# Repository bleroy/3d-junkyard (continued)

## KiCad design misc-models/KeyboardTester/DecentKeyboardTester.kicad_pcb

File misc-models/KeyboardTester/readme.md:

# Decent Retro Keyboard Tester

The Decent Retro Keyboard Tester is an open source board designed around the RP2040 chip
to test vintage computer keyboards.
I built it to test my own modern keyboard replacements for Atari 8-bit computers, but
the architecture is generic enough that drivers for other computers should be very easy
to build.

The tester currently supports the following keyboards:

- Atari 400
- Atari 800
- Atari XE (except XEGS, coming soon)
- Atari 600XL and 800XL
- Atari 1200XL
- USB keyboards

## How to use the tester

Connect the tester to a power source (either the micro-USB at the back or the barrel jack,
center-positive with 5V).

Press the mode button repeatedly until you reach the mode for the keyboard to test.

Connect the keyboard to test.

Start pressing each key on the keyboard. The corresponding LED on the tester should turn
from orange to green. Continue doing that until all the lights are green.

If a light remains orange after the corresponding key has been pressed, there is an issue
with that key. Oftentimes, a whole pattern of keys will fail, not just one.
That usually means that a whole line or column of the keyboard matrix is failing.
Consult a map of the keyboard's matrix and probe the corresponding lines on the PCB or on the
keyboard cable.

## How to build one

### The board

The assembled board can be ordered from JLCPCB or PCBWay using the following files:

- [Gerber](./production/Decent_Retro_Keyboard_Tester_2.zip)
- [BOM](./production/bom.csv)
- [Positions](./production/positions.csv)

You should order the boards assembled, and you'll only have to solder the connectors,
the OLED screen and the barrel jack if you want to power the board without USB.

The connectors are:

- 24P 2.54mm male pin headers on the left of the board
- 15P 2.54mm male pin headers immediately to the right of the 24P connector
- 22P 2.54mm female headers on the top of the board
- 18P 2.54mm male pin headers under the 22P one.
- DB15 at the bottom left of the board
- USB-A connector to the right of the DB25 connector

Don't solder the display yet, as it's easier to do once the board is in the top half of the enclosure.

### The enclosure

Print the following parts:

- 1x [Enclosure top](./Enclosure/Decent%20Retro%20Keyboard%20Tester%20Enclosure-Top.stl)
- 1x [Enclosure bottom](./Enclosure/Decent%20Retro%20Keyboard%20Tester%20Enclosure-Bottom.stl)
- 3x [Button](./Enclosure/Decent%20Retro%20Keyboard%20Tester%20Enclosure-Button.stl)
- 1x [Full light tunnel](./Enclosure/Decent%20Retro%20Keyboard%20Tester%20Enclosure-Light%20tunnels.stl)
- 1x [Switch slider](./Enclosure/Decent%20Retro%20Keyboard%20Tester%20Enclosure-Slider.stl)

Depending on the keyboards you want to test:

- 1x [Atari XE light tunnel](./Enclosure/Decent%20Retro%20Keyboard%20Tester%20Enclosure-ATARI-XE-Light%20tunnels.stl)
- 1x [Atari XL light tunnel](./Enclosure/Decent%20Retro%20Keyboard%20Tester%20Enclosure-ATARI-XL-Light%20tunnels.stl)

Add 4 threaded inserts to the top of the enclosure.

With the top of the enclosure upside-down on your workbench, add the three buttons, put the OLED
screen in position, then add the main board on top of that.

Make sure everything is properly aligned and level, then solder the screen to the board.

Add the slider to the little switch at the back of the board.

Put the bottom of the enclosure in place, then secure everything with 4 screws corresponding to the
threaded inserts you chose.

### Adapter boards

The tester has some connectors built-in, but the ultimate goal is to support a wide variety of
keyboards with exotic connectors.
For instance, Atari XE and XL computers use a single-sided 2.54mm 24 pin connector that is very
hard to source outside of scavenging it from a vintage motherboard.

To address this, the board presents 24 GPIOs on a standard pin header connector so one can build
adapter boards that translate that into specific connectors.

Have the adapter boards you need fabricated and assemble the required connectors on them.

At this moment, the only adapter board is for Atari XE and XL computers:

- [Gerber](./adapter-ATARI-XE-XL/production/adapter-ATARI-XE-XL.zip)

  It can be assembled by adding a 24P 2.54mm female header on the bottom of the board and to the right
  and an Atari keyboard connector on top to the left with the contacts on the left.

### Overlays

Each keyboard driver will do its own mapping of the physical keys to the array of LEDs on the tester.
To make things a little nicer to look at, there are overlays that are made with a printed light tunnel
and a small PCB with windows in the mask layer that let the light get diffused over each key
footprint.

There are overlays available for the following keyboards:

- Atari XE - [Gerber](./Overlays/XE-overlay/production/XE-overlay.zip) & [light tunnel](./Overlays/XE-overlay/Decent%20Retro%20Keyboard%20Tester%20Enclosure-ATARI-XE-Light%20tunnels.stl)
- Atari XL - [Gerber](./Overlays/XL-overlay/production/XL-overlay.zip) & [light tunnel](./Overlays/XL-overlay/Decent%20Retro%20Keyboard%20Tester%20Enclosure-ATARI-XL-Light%20tunnels.stl)

### Flashing the firmware

The tester can be programmed through its micro-usb port on the back.
Connect that port to a computer and it will appear as a disk drive.

There's a one-time operation which is to install CircuitPython on the device.
Get [the latest version for the Pi Pico](https://circuitpython.org/board/raspberry_pi_pico/) and
copy the uf2 file to the root of the device's file system.
The device will reboot and show a new file system.

If at a later date you need to upgrade your CircuitPython, you can do so by keeping the Boot
button pressed while you connect the device to your computer. You'll then be able to copy a new
uf2 file.

Copy the contents of the [firmware](./Firmware/) directory from this repository to the root of
the device.

The tester will reboot and should display some text on the OLED display.
If it doesn't, then something went wrong with the installation.
Verify you copied everything.
If there's still an issue, you can try to check what happens on the serial port using [the Pi Pico
tooling for VS Code](https://marketplace.visualstudio.com/items?itemName=raspberry-pi.raspberry-pi-pico).

## This is too complicated, can I just buy one from you?

Yes, you can. [Contact me on the AtariAge forums](https://forums.atariage.com/profile/76850-screamingattheradio/).

## Design

The controller part of the board is just a simple implementation of [the RP2040 reference board](https://datasheets.raspberrypi.com/rp2040/hardware-design-with-rp2040.pdf).

GPIO 0 and 1 are the data lines for the USB-A port in front of the board.

GPIO 2 to 25 are connected to the various keyboard ports and can be programmed to scan the
keyboard to test. Each connector has its first pin (GPIO 2) towards the top-left of the board.

GPIO26 is connected to the mode button.

GPIO27 is the data line for the addressable RGB LEDs. Each key module has a SK6805 addressable
LED and a 100nF capacitor:

The data out of each LED goes into the data in of the next.
The final data out is exposed on a small 3-pin connector at the back of the board, enabling
the addition of more LEDs.

GPIO28 and 29 are I2C SDA and SCL, connected to the OLED display and to a qwiic expansion port
at the back of the board.

There's also a debug port on the board that can be used with [the Pi debug probe](https://www.raspberrypi.com/documentation/microcontrollers/debug-probe.html).

## Contributions

A great contribution to this project would be new drivers, adapters and overlays for keyboards
not yet supported.

Bug fixes are also greatly appreciated!

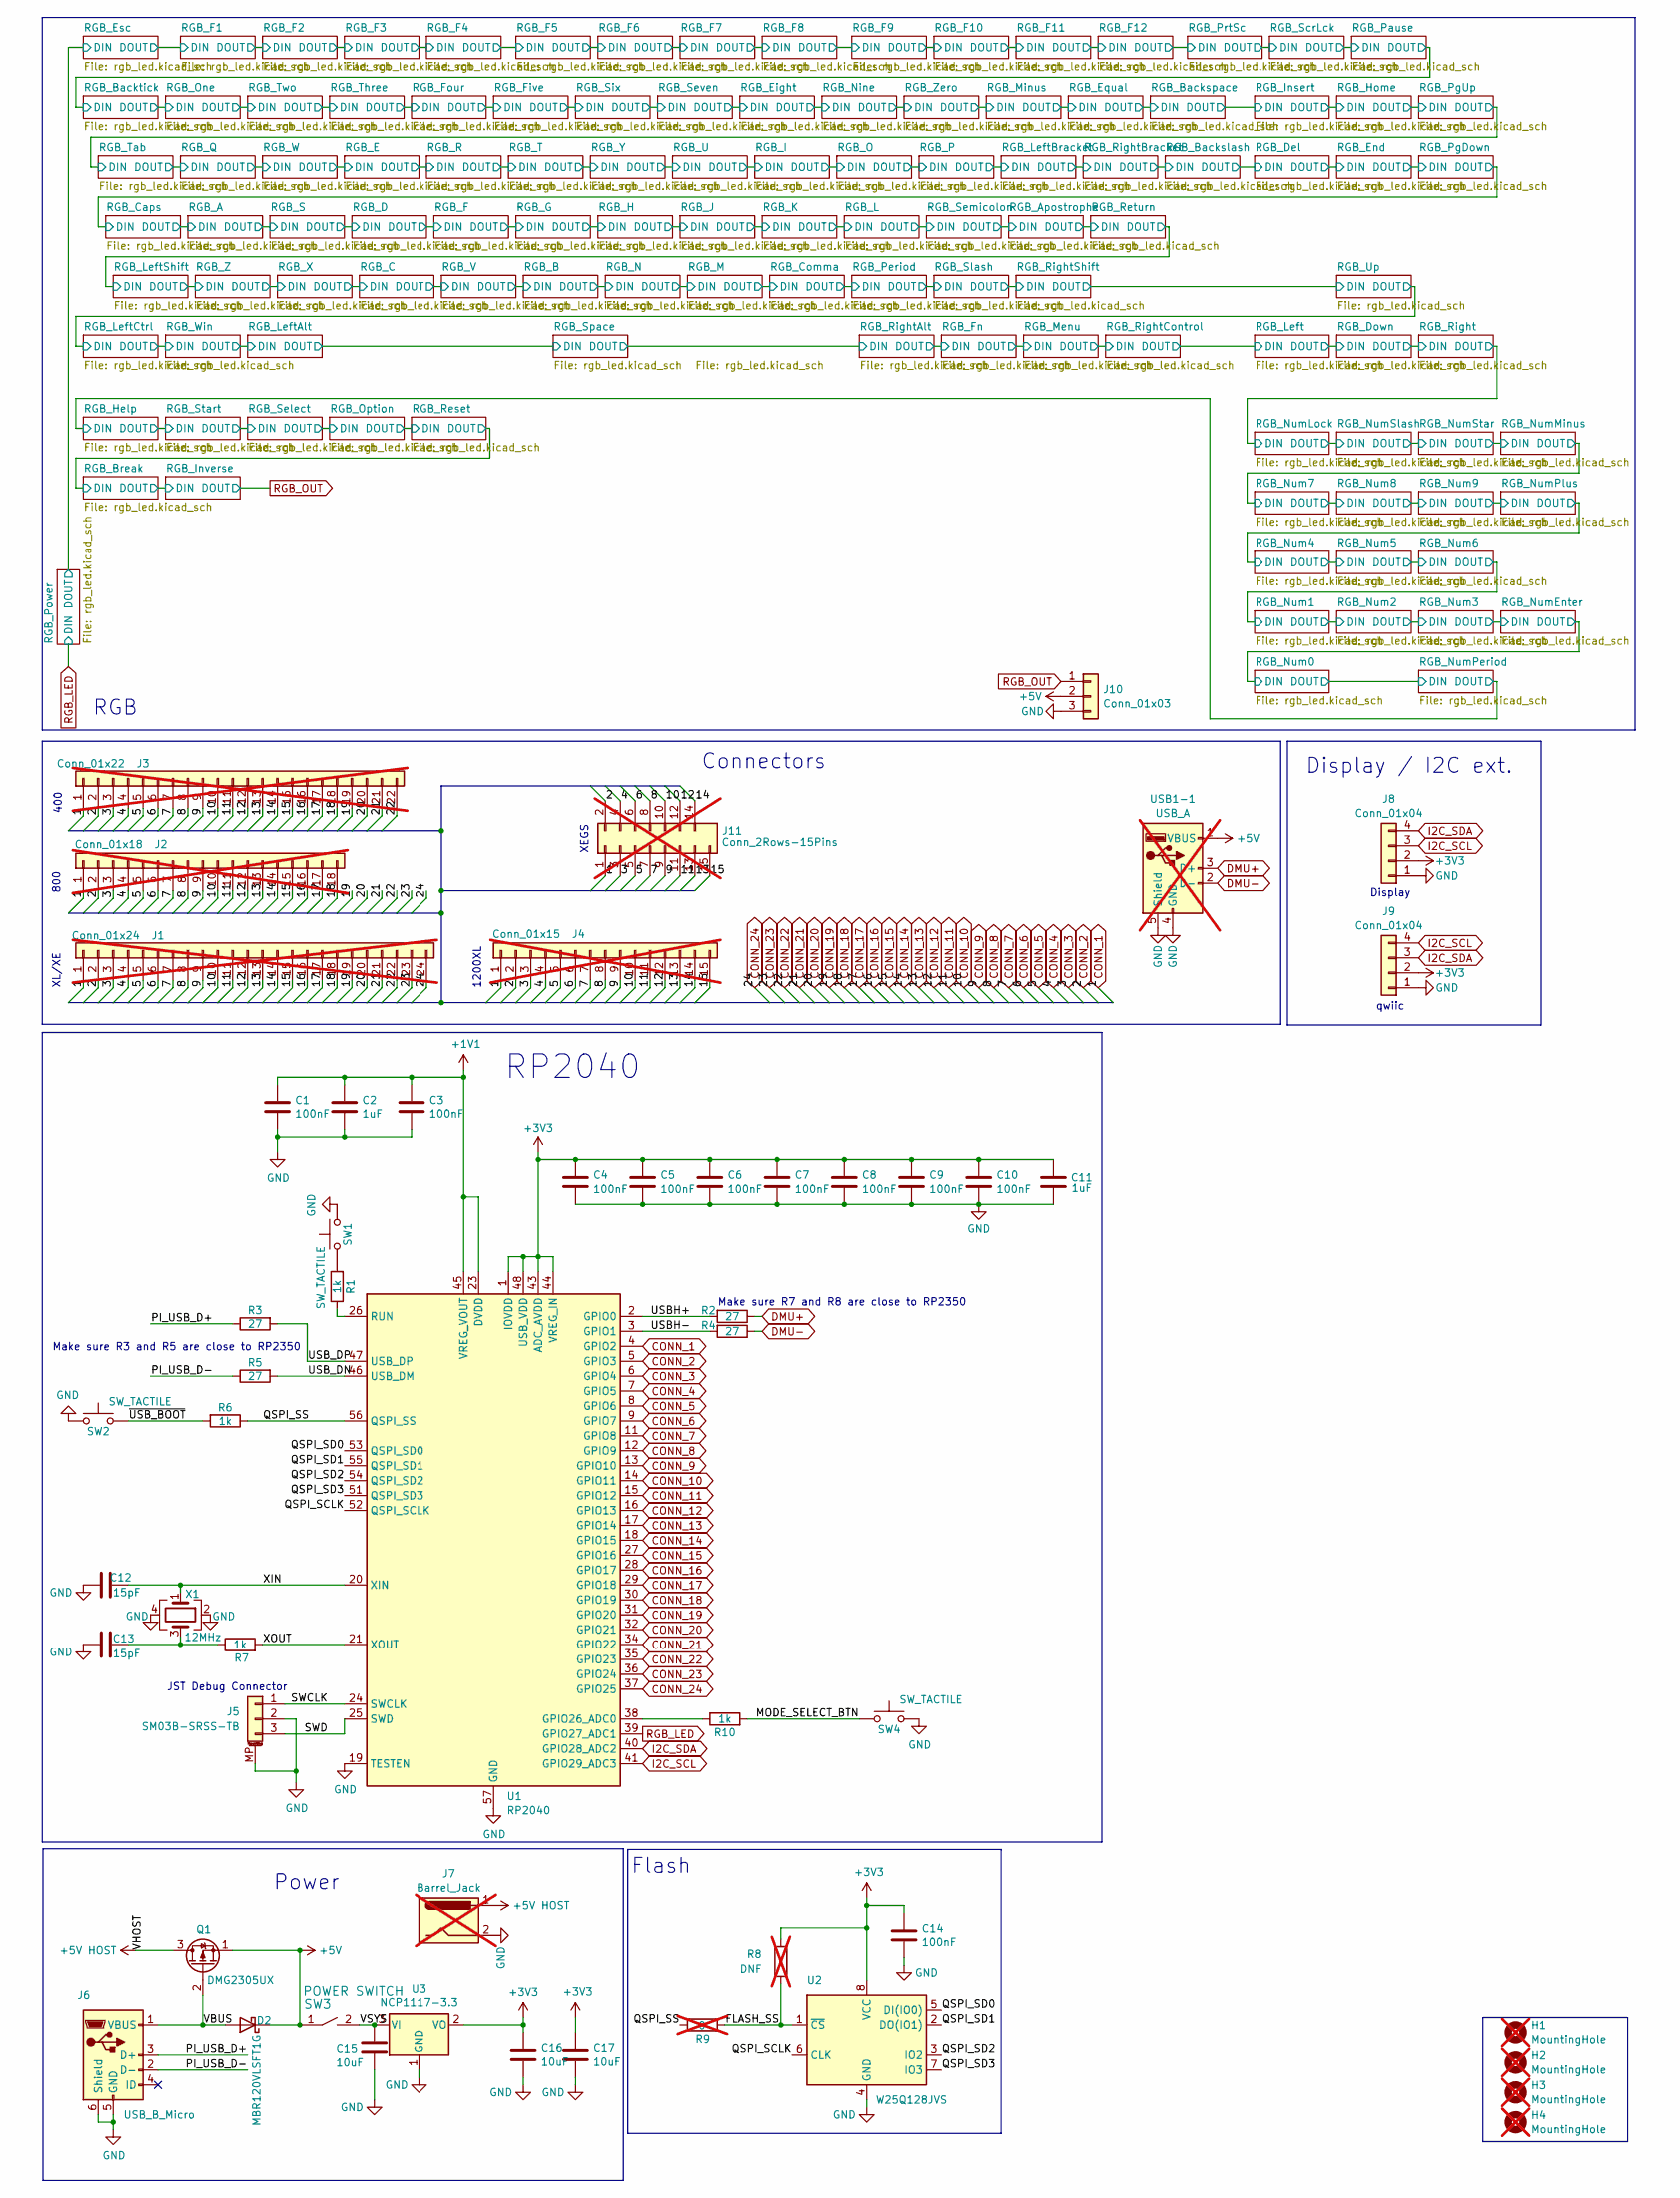
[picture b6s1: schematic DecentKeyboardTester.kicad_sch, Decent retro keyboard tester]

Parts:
C1, C3, C4, C5, C6, C7, C8, C9, C10, C14: 100nF; C_0402_1005Metric; JLCPCB Part # C1525
C2, C11: 1uF; C_0402_1005Metric; JLCPCB Part # C52923
C12, C13: 15pF; C_0402_1005Metric; JLCPCB Part # C1548
C15, C16, C17: 10uF; C_0402_1005Metric; JLCPCB Part # C15525
D2: MBR120VLSFT1G; Nexperia_CFP3_SOD-123W; JLCPCB Part # C8598
H1, H2, H3, H4: MountingHole; MountingHole_2.2mm_M2; not fitted
J1: Conn_01x24; PinSocket_1x24_P2.54mm_Vertical; not fitted
J2: Conn_01x18; PinSocket_1x18_P2.54mm_Vertical; not fitted
J3: Conn_01x22; PinSocket_1x22_P2.54mm_Vertical; not fitted
J4: Conn_01x15; PinSocket_1x15_P2.54mm_Vertical; not fitted
J5: SM03B-SRSS-TB; JST_SH_BM03B-SRSS-TB_1x03-1MP_P1.00mm_Vertical; JLCPCB Part # C160389
J6: USB_B_Micro; USB_Micro-AB_Molex_47590-0001; JLCPCB Part # C505111
J7: Barrel_Jack; BarrelJack_Horizontal; not fitted
J8: Conn_01x04; OLED_modeule_0_91_128x32_I2C
J9: Conn_01x04; JST_SH_SM04B-SRSS-TB_1x04-1MP_P1.00mm_Horizontal; JLCPCB Part # C160390
J10: Conn_01x03; JST_SH_SM03B-SRSS-TB_1x03-1MP_P1.00mm_Horizontal; JLCPCB Part # C160403
J11: Conn_2Rows-15Pins; DSUB-15_Male_Horizontal_P2.77x2.84mm_EdgePinOffset4.94mm_Ho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; not fitted
Q1: DMG2305UX; SOT-23; JLCPCB Part # C150470
R1, R6, R7, R10: 1k; R_0402_1005Metric; JLCPCB Part # C11702
R2, R3, R4, R5: 27; R_0805_2012Metric; JLCPCB Part # C17561
R8: DNF; R_0402_1005Metric; not fitted
R9: 0; SolderJumper-2_P1.3mm_Bridged_RoundedPad1.0x1.5mm; not fitted
SW1, SW2, SW4: SW_TACTILE; Tactile_Switch_Basic_XKB_TS-1187A; JLCPCB Part # C318884
SW3: POWER SWITCH; SW_SPDT_PCM12; JLCPCB Part # C431540
U1: RP2040; QFN-56-1EP_7x7mm_P0.4mm_EP3.2x3.2mm; JLCPCB Part # C2040
U2: W25Q128JVS; SOIC-8_5.23x5.23mm_P1.27mm; JLCPCB Part # C97521
U3: NCP1117-3.3; SOT-223-3_TabPin2; JLCPCB Part # C6186
USB1-1: USB_A; USB_A_Molex_67643_Horizontal; not fitted
X1: 12MHz; Crystal_SMD_Abracon_ABM8AIG-4Pin_3.2x2.5mm; JLCPCB Part # C9002

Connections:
+1V1: C1.1, C2.1, C3.1, U1.23 (DVDD), U1.45 (VREG_VOUT), U1.50 (DVDD)
+3V3: C4.1, C5.1, C6.1, C7.1, C8.1, C9.1, C10.1, C11.1, C14.1, C16.1, C17.1, J8.2, J9.2, R8.1, U1.1 (IOVDD), U1.10 (IOVDD), U1.22 (IOVDD), U1.33 (IOVDD), U1.42 (IOVDD), U1.43 (ADC_AVDD), U1.44 (VREG_IN), U1.48 (USB_VDD), U1.49 (IOVDD), U2.8 (VCC), U3.2 (VO)
+5V: D2.1 (K), J10.2, Q1.1 (S), SW3.1, USB1-1.1 (VBUS); also elsewhere on the board
+5V HOST: J7.1, Q1.3 (D)
/FLASH_SS: R8.2, R9.2, U2.1 (~CS)
/MODE_SELECT_BTN: R10.2, SW4.1
/PI_USB_D+: J6.3 (D+), R3.1
/PI_USB_D-: J6.2 (D-), R5.1
/QSPI_SCLK: U1.52 (QSPI_SCLK), U2.6 (CLK)
/QSPI_SD0: U1.53 (QSPI_SD0), U2.5 (DI(IO0))
/QSPI_SD1: U1.55 (QSPI_SD1), U2.2 (DO(IO1))
/QSPI_SD2: U1.54 (QSPI_SD2), U2.3 (IO2)
/QSPI_SD3: U1.51 (QSPI_SD3), U2.7 (IO3)
/QSPI_SS: R6.1, R9.1, U1.56 (QSPI_SS)
/SWCLK: J5.1, U1.24 (SWCLK)
/SWD: J5.3, U1.25 (SWD)
/USBH+: R2.2, U1.2 (GPIO0)
/USBH-: R4.2, U1.3 (GPIO1)
/USB_DN: R5.2, U1.46 (USB_DM)
/USB_DP: R3.2, U1.47 (USB_DP)
/VBUS: D2.2 (A), J6.1 (VBUS), Q1.2 (G)
/VSYS: C15.1, SW3.2, U3.3 (VI)
/XIN: C12.1, U1.20 (XIN), X1.1
/XOUT: R7.2, U1.21 (XOUT)
/~USB_BOOT: R6.2, SW2.2
CONN_1: J1.1, J2.1, J3.1, J4.1, J11.1, U1.4 (GPIO2)
CONN_2: J1.2, J2.2, J3.2, J4.2, J11.2, U1.5 (GPIO3)
CONN_3: J1.3, J2.3, J3.3, J4.3, J11.3, U1.6 (GPIO4)
CONN_4: J1.4, J2.4, J3.4, J4.4, J11.4, U1.7 (GPIO5)
CONN_5: J1.5, J2.5, J3.5, J4.5, J11.5, U1.8 (GPIO6)
CONN_6: J1.6, J2.6, J3.6, J4.6, J11.6, U1.9 (GPIO7)
CONN_7: J1.7, J2.7, J3.7, J4.7, J11.7, U1.11 (GPIO8)
CONN_8: J1.8, J2.8, J3.8, J4.8, J11.8, U1.12 (GPIO9)
CONN_9: J1.9, J2.9, J3.9, J4.9, J11.9, U1.13 (GPIO10)
CONN_10: J1.10, J2.10, J3.10, J4.10, J11.10, U1.14 (GPIO11)
CONN_11: J1.11, J2.11, J3.11, J4.11, J11.11, U1.15 (GPIO12)
CONN_12: J1.12, J2.12, J3.12, J4.12, J11.12, U1.16 (GPIO13)
CONN_13: J1.13, J2.13, J3.13, J4.13, J11.13, U1.17 (GPIO14)
CONN_14: J1.14, J2.14, J3.14, J4.14, J11.14, U1.18 (GPIO15)
CONN_15: J1.15, J2.15, J3.15, J4.15, J11.15, U1.27 (GPIO16)
CONN_16: J1.16, J2.16, J3.16, U1.28 (GPIO17)
CONN_17: J1.17, J2.17, J3.17, U1.29 (GPIO18)
CONN_18: J1.18, J2.18, J3.18, U1.30 (GPIO19)
CONN_19: J1.19, J3.19, U1.31 (GPIO20)
CONN_20: J1.20, J3.20, U1.32 (GPIO21)
CONN_21: J1.21, J3.21, U1.34 (GPIO22)
CONN_22: J1.22, J3.22, U1.35 (GPIO23)
CONN_23: J1.23, U1.36 (GPIO24)
CONN_24: J1.24, U1.37 (GPIO25)
DMU+: R2.1, USB1-1.3 (D+)
DMU-: R4.1, USB1-1.2 (D-)
GND: C1.2, C2.2, C3.2, C4.2, C5.2, C6.2, C7.2, C8.2, C9.2, C10.2, C11.2, C12.2, C13.1, C14.2, C15.2, C16.2, C17.2, J5.2, J5.MP (MountPin), J6.5 (GND), J6.6 (Shield), J7.2, J8.1, J9.1, J10.3, SW1.2, SW2.1, SW4.2, U1.19 (TESTEN), U1.57 (GND), U2.4 (GND), U3.1 (GND), USB1-1.4 (GND), USB1-1.5 (Shield), X1.2, X1.4; also elsewhere on the board
I2C_SCL: J8.3, J9.4, U1.41 (GPIO29_ADC3)
I2C_SDA: J8.4, J9.3, U1.40 (GPIO28_ADC2)
unnamed: C13.2, R7.1, X1.3
unnamed: R1.2, SW1.1
unnamed: R10.1, U1.38 (GPIO26_ADC0)
unnamed: R1.1, U1.26 (RUN)
RGB_LED: U1.39 (GPIO27_ADC1); also elsewhere on the board
RGB_OUT: J10.1; also elsewhere on the board

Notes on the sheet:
RP2040
XEGS
Display / I2C ext.
Display
400
800
Flash
qwiic
RGB
JST Debug Connector
Connectors
XL/XE
1200XL
Power
Make sure R3 and R5 are close to RP2350
Make sure R7 and R8 are close to RP2350

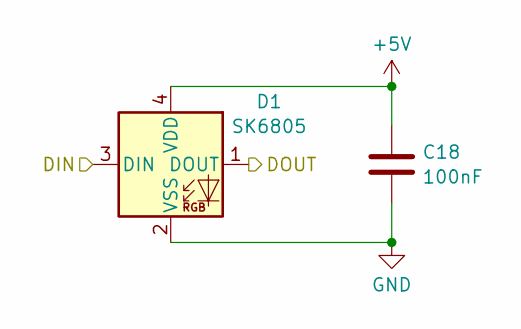
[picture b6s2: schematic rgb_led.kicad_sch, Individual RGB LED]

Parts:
C18: 100nF; C_0402_1005Metric; JLCPCB Part # C1525
D1: SK6805; SK6809-EC15; JLCPCB Part # C2909055

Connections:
+5V: C18.1, D1.4 (VDD); also elsewhere on the board
/RGB_Esc/DOUT: D1.3 (DIN); also elsewhere on the board
/RGB_F1/DOUT: D1.1 (DOUT); also elsewhere on the board
GND: C18.2, D1.2 (VSS); also elsewhere on the board

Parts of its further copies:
C19, C20, C21, C22, C23, C24, C25, C26, C27, C28, C29, C30, C31, C32, C33, C34, C35, C36, C37, C38, C39, C40, C41, C42, C43, C44, C45, C46, C47, C48, C49, C50, C51, C52, C53, C54, C55, C56, C57, C58, C59, C60, C61, C62, C63, C64, C65, C66, C67, C68, C69, C70, C71, C72, C73, C74, C75, C76, C77, C78, C79, C80, C81, C82, C83, C84, C85, C86, C87, C88, C89, C90, C91, C92, C93, C94, C95, C96, C97, C98, C99, C100, C101, C102, C103, C104, C105, C106, C107, C108, C109, C110, C111, C112, C113, C114, C115, C116, C117, C118, C119, C120, C121, C122, C123, C124, C125, C126, C127, C128, C129: 100nF; C_0402_1005Metric; JLCPCB Part # C1525
D3, D4, D5, D6, D7, D8, D9, D10, D11, D12, D13, D14, D15, D16, D17, D18, D19, D20, D21, D22, D23, D24, D25, D26, D27, D28, D29, D30, D31, D32, D33, D34, D35, D36, D37, D38, D39, D40, D41, D42, D43, D44, D45, D46, D47, D48, D49, D50, D51, D52, D53, D54, D55, D56, D57, D58, D59, D60, D61, D62, D63, D64, D65, D66, D67, D68, D69, D70, D71, D72, D73, D74, D75, D76, D77, D78, D79, D80, D81, D82, D83, D84, D85, D86, D87, D88, D89, D90, D91, D92, D93, D94, D95, D96, D97, D98, D99, D100, D101, D102, D103, D104, D105, D106, D107, D108, D109, D110, D111, D112, D113: SK6805; SK6809-EC15; JLCPCB Part # C2909055

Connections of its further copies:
+5V: C19.1, C20.1, C21.1, C22.1, C23.1, C24.1, C25.1, C26.1, C27.1, C28.1, C29.1, C30.1, C31.1, C32.1, C33.1, C34.1, C35.1, C36.1, C37.1, C38.1, C39.1, C40.1, C41.1, C42.1, C43.1, C44.1, C45.1, C46.1, C47.1, C48.1, C49.1, C50.1, C51.1, C52.1, C53.1, C54.1, C55.1, C56.1, C57.1, C58.1, C59.1, C60.1, C61.1, C62.1, C63.1, C64.1, C65.1, C66.1, C67.1, C68.1, C69.1, C70.1, C71.1, C72.1, C73.1, C74.1, C75.1, C76.1, C77.1, C78.1, C79.1, C80.1, C81.1, C82.1, C83.1, C84.1, C85.1, C86.1, C87.1, C88.1, C89.1, C90.1, C91.1, C92.1, C93.1, C94.1, C95.1, C96.1, C97.1, C98.1, C99.1, C100.1, C101.1, C102.1, C103.1, C104.1, C105.1, C106.1, C107.1, C108.1, C109.1, C110.1, C111.1, C112.1, C113.1, C114.1, C115.1, C116.1, C117.1, C118.1, C119.1, C120.1, C121.1, C122.1, C123.1, C124.1, C125.1, C126.1, C127.1, C128.1, C129.1, D3.4 (VDD), D4.4 (VDD), D5.4 (VDD), D6.4 (VDD), D7.4 (VDD), D8.4 (VDD), D9.4 (VDD), D10.4 (VDD), D11.4 (VDD), D12.4 (VDD), D13.4 (VDD), D14.4 (VDD), D15.4 (VDD), D16.4 (VDD), D17.4 (VDD), D18.4 (VDD), D19.4 (VDD), D20.4 (VDD), D21.4 (VDD), D22.4 (VDD), D23.4 (VDD), D24.4 (VDD), D25.4 (VDD), D26.4 (VDD), D27.4 (VDD), D28.4 (VDD), D29.4 (VDD), D30.4 (VDD), D31.4 (VDD), D32.4 (VDD), D33.4 (VDD), D34.4 (VDD), D35.4 (VDD), D36.4 (VDD), D37.4 (VDD), D38.4 (VDD), D39.4 (VDD), D40.4 (VDD), D41.4 (VDD), D42.4 (VDD), D43.4 (VDD), D44.4 (VDD), D45.4 (VDD), D46.4 (VDD), D47.4 (VDD), D48.4 (VDD), D49.4 (VDD), D50.4 (VDD), D51.4 (VDD), D52.4 (VDD), D53.4 (VDD), D54.4 (VDD), D55.4 (VDD), D56.4 (VDD), D57.4 (VDD), D58.4 (VDD), D59.4 (VDD), D60.4 (VDD), D61.4 (VDD), D62.4 (VDD), D63.4 (VDD), D64.4 (VDD), D65.4 (VDD), D66.4 (VDD), D67.4 (VDD), D68.4 (VDD), D69.4 (VDD), D70.4 (VDD), D71.4 (VDD), D72.4 (VDD), D73.4 (VDD), D74.4 (VDD), D75.4 (VDD), D76.4 (VDD), D77.4 (VDD), D78.4 (VDD), D79.4 (VDD), D80.4 (VDD), D81.4 (VDD), D82.4 (VDD), D83.4 (VDD), D84.4 (VDD), D85.4 (VDD), D86.4 (VDD), D87.4 (VDD), D88.4 (VDD), D89.4 (VDD), D90.4 (VDD), D91.4 (VDD), D92.4 (VDD), D93.4 (VDD), D94.4 (VDD), D95.4 (VDD), D96.4 (VDD), D97.4 (VDD), D98.4 (VDD), D99.4 (VDD), D100.4 (VDD), D101.4 (VDD), D102.4 (VDD), D103.4 (VDD), D104.4 (VDD), D105.4 (VDD), D106.4 (VDD), D107.4 (VDD), D108.4 (VDD), D109.4 (VDD), D110.4 (VDD), D111.4 (VDD), D112.4 (VDD), D113.4 (VDD); also elsewhere on the board
/RGB_A/DIN: D57.3 (DIN), D61.1 (DOUT)
/RGB_A/DOUT: D57.1 (DOUT), D63.3 (DIN)
/RGB_Apostrophe/DIN: D54.3 (DIN), D56.1 (DOUT)
/RGB_Apostrophe/DOUT: D54.1 (DOUT), D59.3 (DIN)
/RGB_B/DIN: D69.1 (DOUT), D70.3 (DIN)
/RGB_B/DOUT: D70.1 (DOUT), D71.3 (DIN)
/RGB_Backslash/DIN: D35.3 (DIN), D38.1 (DOUT)
/RGB_Backslash/DOUT: D35.1 (DOUT), D42.3 (DIN)
/RGB_Backspace/DIN: D30.1 (DOUT), D31.3 (DIN)
/RGB_Backspace/DOUT: D31.1 (DOUT), D32.3 (DIN)
/RGB_Backtick/DIN: D17.1 (DOUT), D18.3 (DIN)
/RGB_Backtick/DOUT: D18.1 (DOUT), D19.3 (DIN)
/RGB_Break/DIN: D110.1 (DOUT), D112.3 (DIN)
/RGB_Break/DOUT: D111.3 (DIN), D112.1 (DOUT)
/RGB_C/DIN: D68.3 (DIN), D76.1 (DOUT)
/RGB_C/DOUT: D68.1 (DOUT), D69.3 (DIN)
/RGB_Caps/DIN: D46.1 (DOUT), D61.3 (DIN)
/RGB_Comma/DIN: D72.1 (DOUT), D73.3 (DIN)
/RGB_Comma/DOUT: D73.1 (DOUT), D74.3 (DIN)
/RGB_D/DIN: D52.3 (DIN), D63.1 (DOUT)
/RGB_D/DOUT: D52.1 (DOUT), D58.3 (DIN)
/RGB_Del/DOUT: D41.3 (DIN), D42.1 (DOUT)
/RGB_Down/DIN: D85.3 (DIN), D86.1 (DOUT)
/RGB_Down/DOUT: D85.1 (DOUT), D87.3 (DIN)
/RGB_E/DIN: D49.3 (DIN), D50.1 (DOUT)
/RGB_E/DOUT: D40.3 (DIN), D49.1 (DOUT)
/RGB_Eight/DIN: D25.1 (DOUT), D26.3 (DIN)
/RGB_Eight/DOUT: D26.1 (DOUT), D27.3 (DIN)
/RGB_End/DOUT: D41.1 (DOUT), D46.3 (DIN)
/RGB_Equal/DIN: D29.1 (DOUT), D30.3 (DIN)
/RGB_Esc/DIN: D14.3 (DIN), D113.1 (DOUT)
/RGB_Esc/DOUT: D14.1 (DOUT); also elsewhere on the board
/RGB_F1/DOUT: D3.3 (DIN); also elsewhere on the board
/RGB_F2/DOUT: D3.1 (DOUT), D4.3 (DIN)
/RGB_F3/DOUT: D4.1 (DOUT), D5.3 (DIN)
/RGB_F4/DOUT: D5.1 (DOUT), D6.3 (DIN)
/RGB_F5/DOUT: D6.1 (DOUT), D7.3 (DIN)
/RGB_F6/DOUT: D7.1 (DOUT), D8.3 (DIN)
/RGB_F7/DOUT: D8.1 (DOUT), D9.3 (DIN)
/RGB_F8/DOUT: D9.1 (DOUT), D10.3 (DIN)
/RGB_F10/DIN: D10.1 (DOUT), D11.3 (DIN)
/RGB_F10/DOUT: D11.1 (DOUT), D12.3 (DIN)
/RGB_F11/DOUT: D12.1 (DOUT), D13.3 (DIN)
/RGB_F12/DOUT: D13.1 (DOUT), D15.3 (DIN)
/RGB_F/DOUT: D58.1 (DOUT), D60.3 (DIN)
/RGB_Five/DIN: D22.1 (DOUT), D23.3 (DIN)
/RGB_Five/DOUT: D23.1 (DOUT), D24.3 (DIN)
/RGB_Fn/DIN: D78.3 (DIN), D88.1 (DOUT)
/RGB_Fn/DOUT: D78.1 (DOUT), D83.3 (DIN)
/RGB_Four/DIN: D21.1 (DOUT), D22.3 (DIN)
/RGB_G/DOUT: D60.1 (DOUT), D64.3 (DIN)
/RGB_H/DOUT: D62.3 (DIN), D64.1 (DOUT)
/RGB_Help/DIN: D105.1 (DOUT), D106.3 (DIN)
/RGB_Help/DOUT: D106.1 (DOUT), D107.3 (DIN)
/RGB_Home/DIN: D32.1 (DOUT), D33.3 (DIN)
/RGB_Home/DOUT: D33.1 (DOUT), D34.3 (DIN)
/RGB_I/DIN: D37.3 (DIN), D47.1 (DOUT)
/RGB_I/DOUT: D37.1 (DOUT), D44.3 (DIN)
/RGB_J/DOUT: D53.3 (DIN), D62.1 (DOUT)
/RGB_K/DOUT: D53.1 (DOUT), D55.3 (DIN)
/RGB_L/DOUT: D55.1 (DOUT), D56.3 (DIN)
/RGB_Left/DIN: D82.1 (DOUT), D86.3 (DIN)
/RGB_LeftAlt/DIN: D89.3 (DIN), D90.1 (DOUT)
/RGB_LeftAlt/DOUT: D79.3 (DIN), D89.1 (DOUT)
/RGB_LeftBracket/DIN: D43.3 (DIN), D51.1 (DOUT)
/RGB_LeftBracket/DOUT: D38.3 (DIN), D43.1 (DOUT)
/RGB_LeftCtrl/DIN: D75.1 (DOUT), D81.3 (DIN)
/RGB_LeftCtrl/DOUT: D81.1 (DOUT), D90.3 (DIN)
/RGB_LeftShift/DIN: D59.1 (DOUT), D67.3 (DIN)
/RGB_LeftShift/DOUT: D65.3 (DIN), D67.1 (DOUT)
/RGB_M/DIN: D71.1 (DOUT), D72.3 (DIN)
/RGB_Menu/DOUT: D82.3 (DIN), D83.1 (DOUT)
/RGB_Minus/DIN: D28.1 (DOUT), D29.3 (DIN)
/RGB_Nine/DOUT: D27.1 (DOUT), D28.3 (DIN)
/RGB_Num0/DIN: D103.1 (DOUT), D104.3 (DIN)
/RGB_Num0/DOUT: D104.1 (DOUT), D105.3 (DIN)
/RGB_Num1/DIN: D99.1 (DOUT), D100.3 (DIN)
/RGB_Num1/DOUT: D100.1 (DOUT), D101.3 (DIN)
/RGB_Num2/DOUT: D101.1 (DOUT), D102.3 (DIN)
/RGB_Num3/DOUT: D102.1 (DOUT), D103.3 (DIN)
/RGB_Num4/DIN: D96.1 (DOUT), D97.3 (DIN)
/RGB_Num4/DOUT: D97.1 (DOUT), D98.3 (DIN)
/RGB_Num5/DOUT: D98.1 (DOUT), D99.3 (DIN)
/RGB_Num7/DIN: D92.1 (DOUT), D93.3 (DIN)
/RGB_Num7/DOUT: D93.1 (DOUT), D95.3 (DIN)
/RGB_Num8/DOUT: D94.3 (DIN), D95.1 (DOUT)
/RGB_Num9/DOUT: D94.1 (DOUT), D96.3 (DIN)
/RGB_NumLock/DIN: D80.3 (DIN), D87.1 (DOUT)
/RGB_NumLock/DOUT: D80.1 (DOUT), D84.3 (DIN)
/RGB_NumMinus/DIN: D91.1 (DOUT), D92.3 (DIN)
/RGB_NumSlash/DOUT: D84.1 (DOUT), D91.3 (DIN)
/RGB_O/DOUT: D44.1 (DOUT), D51.3 (DIN)
/RGB_One/DOUT: D19.1 (DOUT), D20.3 (DIN)
/RGB_Option/DIN: D108.1 (DOUT), D109.3 (DIN)
/RGB_Option/DOUT: D109.1 (DOUT), D110.3 (DIN)
/RGB_Pause/DIN: D16.1 (DOUT), D17.3 (DIN)
/RGB_Period/DOUT: D74.1 (DOUT), D77.3 (DIN)
/RGB_PgUp/DOUT: D34.1 (DOUT), D36.3 (DIN)
/RGB_PrtSc/DOUT: D15.1 (DOUT), D16.3 (DIN)
/RGB_Q/DIN: D36.1 (DOUT), D45.3 (DIN)
/RGB_Q/DOUT: D45.1 (DOUT), D50.3 (DIN)
/RGB_R/DOUT: D39.3 (DIN), D40.1 (DOUT)
/RGB_RightAlt/DIN: D79.1 (DOUT), D88.3 (DIN)
/RGB_RightShift/DIN: D66.3 (DIN), D77.1 (DOUT)
/RGB_RightShift/DOUT: D66.1 (DOUT), D75.3 (DIN)
/RGB_Select/DIN: D107.1 (DOUT), D108.3 (DIN)
/RGB_Seven/DIN: D24.1 (DOUT), D25.3 (DIN)
/RGB_T/DOUT: D39.1 (DOUT), D48.3 (DIN)
/RGB_Three/DIN: D20.1 (DOUT), D21.3 (DIN)
/RGB_U/DIN: D47.3 (DIN), D48.1 (DOUT)
/RGB_X/DIN: D65.1 (DOUT), D76.3 (DIN)
GND: C19.2, C20.2, C21.2, C22.2, C23.2, C24.2, C25.2, C26.2, C27.2, C28.2, C29.2, C30.2, C31.2, C32.2, C33.2, C34.2, C35.2, C36.2, C37.2, C38.2, C39.2, C40.2, C41.2, C42.2, C43.2, C44.2, C45.2, C46.2, C47.2, C48.2, C49.2, C50.2, C51.2, C52.2, C53.2, C54.2, C55.2, C56.2, C57.2, C58.2, C59.2, C60.2, C61.2, C62.2, C63.2, C64.2, C65.2, C66.2, C67.2, C68.2, C69.2, C70.2, C71.2, C72.2, C73.2, C74.2, C75.2, C76.2, C77.2, C78.2, C79.2, C80.2, C81.2, C82.2, C83.2, C84.2, C85.2, C86.2, C87.2, C88.2, C89.2, C90.2, C91.2, C92.2, C93.2, C94.2, C95.2, C96.2, C97.2, C98.2, C99.2, C100.2, C101.2, C102.2, C103.2, C104.2, C105.2, C106.2, C107.2, C108.2, C109.2, C110.2, C111.2, C112.2, C113.2, C114.2, C115.2, C116.2, C117.2, C118.2, C119.2, C120.2, C121.2, C122.2, C123.2, C124.2, C125.2, C126.2, C127.2, C128.2, C129.2, D3.2 (VSS), D4.2 (VSS), D5.2 (VSS), D6.2 (VSS), D7.2 (VSS), D8.2 (VSS), D9.2 (VSS), D10.2 (VSS), D11.2 (VSS), D12.2 (VSS), D13.2 (VSS), D14.2 (VSS), D15.2 (VSS), D16.2 (VSS), D17.2 (VSS), D18.2 (VSS), D19.2 (VSS), D20.2 (VSS), D21.2 (VSS), D22.2 (VSS), D23.2 (VSS), D24.2 (VSS), D25.2 (VSS), D26.2 (VSS), D27.2 (VSS), D28.2 (VSS), D29.2 (VSS), D30.2 (VSS), D31.2 (VSS), D32.2 (VSS), D33.2 (VSS), D34.2 (VSS), D35.2 (VSS), D36.2 (VSS), D37.2 (VSS), D38.2 (VSS), D39.2 (VSS), D40.2 (VSS), D41.2 (VSS), D42.2 (VSS), D43.2 (VSS), D44.2 (VSS), D45.2 (VSS), D46.2 (VSS), D47.2 (VSS), D48.2 (VSS), D49.2 (VSS), D50.2 (VSS), D51.2 (VSS), D52.2 (VSS), D53.2 (VSS), D54.2 (VSS), D55.2 (VSS), D56.2 (VSS), D57.2 (VSS), D58.2 (VSS), D59.2 (VSS), D60.2 (VSS), D61.2 (VSS), D62.2 (VSS), D63.2 (VSS), D64.2 (VSS), D65.2 (VSS), D66.2 (VSS), D67.2 (VSS), D68.2 (VSS), D69.2 (VSS), D70.2 (VSS), D71.2 (VSS), D72.2 (VSS), D73.2 (VSS), D74.2 (VSS), D75.2 (VSS), D76.2 (VSS), D77.2 (VSS), D78.2 (VSS), D79.2 (VSS), D80.2 (VSS), D81.2 (VSS), D82.2 (VSS), D83.2 (VSS), D84.2 (VSS), D85.2 (VSS), D86.2 (VSS), D87.2 (VSS), D88.2 (VSS), D89.2 (VSS), D90.2 (VSS), D91.2 (VSS), D92.2 (VSS), D93.2 (VSS), D94.2 (VSS), D95.2 (VSS), D96.2 (VSS), D97.2 (VSS), D98.2 (VSS), D99.2 (VSS), D100.2 (VSS), D101.2 (VSS), D102.2 (VSS), D103.2 (VSS), D104.2 (VSS), D105.2 (VSS), D106.2 (VSS), D107.2 (VSS), D108.2 (VSS), D109.2 (VSS), D110.2 (VSS), D111.2 (VSS), D112.2 (VSS), D113.2 (VSS); also elsewhere on the board
RGB_LED: D113.3 (DIN); also elsewhere on the board
RGB_OUT: D111.1 (DOUT); also elsewhere on the board

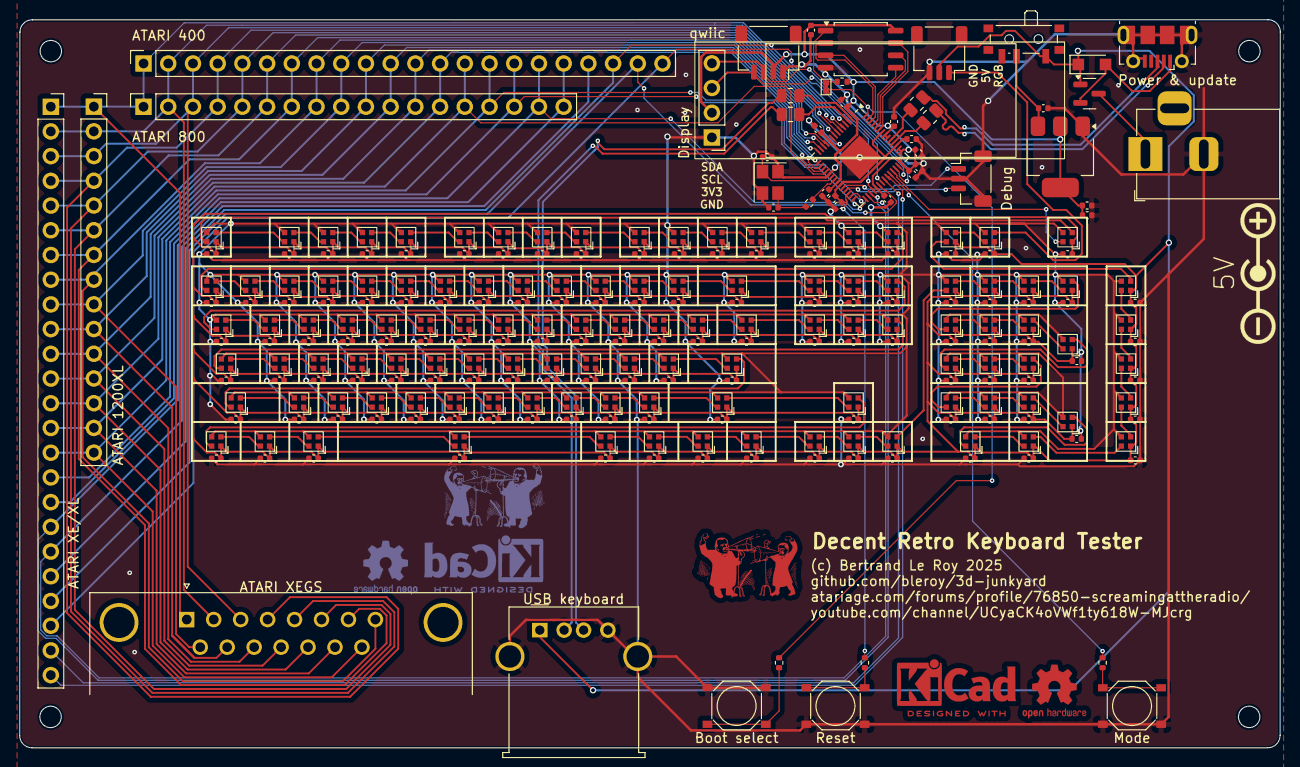
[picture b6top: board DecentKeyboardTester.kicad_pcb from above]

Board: 2 copper layers, 129.6 x 74.8 mm, 277 parts (0 on the bottom side), 171 nets.

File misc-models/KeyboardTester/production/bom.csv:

Designator,Footprint,Quantity,Value,LCSC Part #
"C1, C10, C100, C101, C102, C103, C104, C105, C106, C107, C108, C109, C110, C111, C112, C113, C114, C115, C116, C117, C118, C119, C120, C121, C122, C123, C124, C125, C126, C127, C128, C129, C14, C18, C19, C20, C21, C22, C23, C24, C25, C26, C27, C28, C29, C3, C30, C31, C32, C33, C34, C35, C36, C37, C38, C39, C4, C40, C41, C42, C43, C44, C45, C46, C47, C48, C49, C5, C50, C51, C52, C53, C54, C55, C56, C57, C58, C59, C6, C60, C61, C62, C63, C64, C65, C66, C67, C68, C69, C7, C70, C71, C72, C73, C74, C75, C76, C77, C78, C79, C8, C80, C81, C82, C83, C84, C85, C86, C87, C88, C89, C9, C90, C91, C92, C93, C94, C95, C96, C97, C98, C99",0402,122,100nF,C1525
"C11, C2",0402,2,1uF,C52923
"C12, C13",0402,2,15pF,C1548
"C15, C16, C17",0402,3,10uF,C15525
"D1, D10, D100, D101, D102, D103, D104, D105, D106, D107, D108, D109, D11, D110, D111, D112, D113, D12, D13, D14, D15, D16, D17, D18, D19, D20, D21, D22, D23, D24, D25, D26, D27, D28, D29, D3, D30, D31, D32, D33, D34, D35, D36, D37, D38, D39, D4, D40, D41, D42, D43, D44, D45, D46, D47, D48, D49, D5, D50, D51, D52, D53, D54, D55, D56, D57, D58, D59, D6, D60, D61, D62, D63, D64, D65, D66, D67, D68, D69, D7, D70, D71, D72, D73, D74, D75, D76, D77, D78, D79, D8, D80, D81, D82, D83, D84, D85, D86, D87, D88, D89, D9, D90, D91, D92, D93, D94, D95, D96, D97, D98, D99",SK6809-EC15,112,SK6805,C2909055
D2,Nexperia_CFP3_SOD-123W,1,MBR120VLSFT1G,C8598
J10,JST_SH_SM03B-SRSS-TB_1x03-1MP_P1.00mm_Horizontal,1,Conn_01x03,C160403
J5,JST_SH_BM03B-SRSS-TB_1x03-1MP_P1.00mm_Vertical,1,SM03B-SRSS-TB,C160389
J6,USB_Micro-B_Molex-105017-0001,1,USB_B_Micro,C505111
Q1,SOT-23,1,DMG2305UX,C150470
"R1, R10, R6, R7",0402,4,1k,C11702
"R2, R3, R4, R5",0805,4,27,C17561
"SW1, SW2, SW4",Tactile_Switch_Basic_XKB_TS-1187A,3,SW_TACTILE,C318884
SW3,SW_SPDT_PCM12,1,POWER SWITCH,C431540
U1,QFN-56-1EP_7x7mm_P0.4mm_EP3.2x3.2mm,1,RP2040,C2040
U2,SOIC-8_5.23x5.23mm_P1.27mm,1,W25Q128JVS,C97521
U3,SOT-223-3_TabPin2,1,NCP1117-3.3,C6186
X1,Crystal_SMD_Abracon_ABM8AIG-4Pin_3.2x2.5mm,1,12MHz,C9002
